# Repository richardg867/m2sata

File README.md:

# M.2 SATA Port Reclaimer

This M.2 2280 M-key card allows you to reclaim SATA ports that your motherboard may have as part of the chipset, but are not broken out to SATA connectors since the chipset shares their pins with the M.2 slot's PCI Express lanes.

Each SATA port is connected to a data lane of the M.2 card, although not all motherboards and M.2 slots support more than one SATA port (lane 0); if you just want one port, this adapter can work, but there are off-the-shelf ones that will also do the job. Read on for compatibility information.

## Ordering

I am not going to be offering assembled boards for the foreseeable future, since shipping from Brazil is too expensive and takes too much paperwork. You can order boards from your PCB vendor of choice (Gerber files are in the `gerbers` directory) and assemble them yourself (no SMD work is required); **make sure the PCB thickness is 0.8mm** and the total size is 22mm x 80mm, and go for ENIG finish if possible for best signal integrity (standard HASL finish is untested).

## Bill of materials

The only BOM item is a vertical through-hole SATA data connector, quantity 1 to 4 according to your needs. I've had success with [**LCSC part C2926857**](https://lcsc.com/product-detail/Card-Edge-Connectors_LOTES-ABA-SAT-010-K15_C2926857.html), though replacements can be [easily found](https://gist.github.com/CRImier/d78ff224db0d781627f211ff5cede573), or even desoldered from a donor board. When considering a replacement, make sure its **retention pins are centered** (aligned with the data pins); some parts have one of the retention pins slightly offset.

## Motherboard support

This adapter is expected to work (i.e. provide access to more than one SATA port) on a **SATA+NVMe M.2 slot** on the motherboard platforms listed below. Note that actual compatibility is **at your own risk**; boards might use an external switch chip to route only a single SATA port to the M.2 slot, or they might not have the SATA/PCIe mode switching signals hooked up for all lanes, or the BIOS might not enable normally-unused SATA ports.

In my limited real world testing with the ASUS H170-PLUS D3 (2 SATA ports routed to a single M.2), a drive attached to the second port was not visible in BIOS menus, but it was still initialized by the BIOS and detected by the operating system.

* **Chipsets:**
  * **AMD B550:** Up to 2 ports (0 and 1) from a slot connected to the chipset ("Group 2" - second set of PCIe lanes).
  * **AMD X570, 600 series:** Up to 4 ports from a slot connected to the chipset (combo lanes: [X570](https://www.gamersnexus.net/images/media/2020/amd-chipsets-b550/amd-x570-pcie-lanes.png), [B650](https://images.anandtech.com/doci/17585/SoC_26.png), [X670](https://images.anandtech.com/doci/17585/SoC_25.png)\).
  * **Intel 300/400 series:** Up to 4 ports from a slot connected to the chipset ([HSIO lanes 14-17, 28-21 or 22-25](https://www.intel.com/content/dam/www/public/us/en/documents/datasheets/300-series-chipset-pch-datasheet-vol-1.pdf#page=30)\).
  * **Intel 500/600/700 series:** Up to 4 ports from a slot connected to the chipset ([HSIO lanes 22-25, 26-29](https://edc.intel.com/content/www/us/en/design/ipla/software-development-platforms/client/platforms/alder-lake-desktop/intel-600-series-chipset-family-platform-controller-hub-pch-datasheet-volume/004/intel-600-series-chipset-family-pch/) or (500 only) [30-33](https://cdrdv2.intel.com/v1/dl/getContent/635218)\).
  * **Older stuff:** Some older motherboards which hijack multiple chipset SATA ports for M.2 can make use of this adapter. One example is the aforementioned ASUS H170-PLUS D3, which only exposes 4 of the 6 SATA ports provided by the H170 chipset, with the remaining 2 routed to M.2 slot lanes 0 and 1.
* **CPUs:**
  * **AMD AM4:** Up to 2 ports (0 and 1) from a slot connected to the CPU. Note that most motherboards already expose these (2 SATA ports shared with the CPU M.2 slot), making this adapter redundant.
  
### Very technical stuff: polarity inversion
  
One quirk of SATA is that its B (receive) differential pair has a different polarity than that of the A (transmit) pair or PCI Express RX/TX pairs, and unlike most PCIe implementations, it does *not* tolerate polarity inversion. Since the chipset's SerDes expects the same lane polarities in both SATA and PCIe modes, motherboards account for this quirk by inverting the polarity of the first SATA/PCIe lane going to the M.2 slot, to satisfy both SATA (cannot be inverted) and PCIe (can be inverted):

| M.2 pin | PCB | Chipset pin |
| ---: | :---: | :--- |
| PCIe TX0+ or SATA A+ | 🡸 | PCIe TX0+ or SATA A+ |
| PCIe TX0- or SATA A- | 🡸 | PCIe TX0- or SATA A- |
| PCIe **RX0+** or SATA **B-** | 🡾 | PCIe **RX0+** or SATA **B+** |
| PCIe **RX0-** or SATA **B+** | 🡽 | PCIe **RX0-** or SATA **B-** |
| PCIe TXn+ | 🡸 | PCIe TXn+ or SATA A+ |
| PCIe TXn- | 🡸 | PCIe TXn- or SATA A- |
| PCIe **RXn+** | 🡺 |PCIe RXn+ or SATA **B+** |
| PCIe **RXn-** | 🡺 | PCIe RXn- or SATA **B-** |

Since I have yet to see a motherboard which inverts the RX polarity on *all lanes* (not just lane 0), this card inverts it on lanes 1-3 so that they can work properly in SATA mode. If you get connection errors (Linux dmesg: `SATA link down (SStatus 1 SControl 300)`) on ports 1-3 even with high quality cables, you somehow have a motherboard which also inverts lanes 1-3; if you're feeling adventurous, the [jumperable](https://github.com/richardg867/m2sata/tree/jumperable) branch has a special variant of this card with jumper links to configure RX polarities at will.

## Acknowledgements

Huge thanks to [Arya](https://github.com/CRImier) for helping me with the design (using their [nvme_to_dual_ssd](https://github.com/CRImier/MyKiCad/tree/master/Laptop%20mods/nvme_to_dual_ssd) card as a base) and prototyping of this project.

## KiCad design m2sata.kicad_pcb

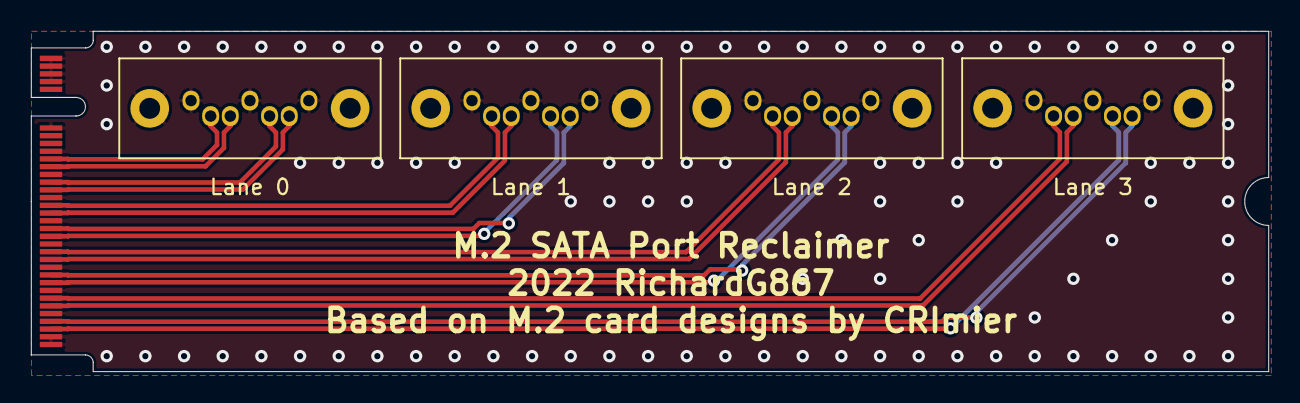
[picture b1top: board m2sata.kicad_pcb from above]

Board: 2 copper layers, 80.0 x 22.0 mm, 5 parts (0 on the bottom side), 17 nets.

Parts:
J1, J2, J3, J4: SATA; SATA-7_THT_VERT_1
U1: IN; NGFF_M

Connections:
/SATA1_A+: J1.2, U1.49 (PET0+/A+)
/SATA1_A-: J1.3, U1.47 (PET0-/A-)
/SATA1_B+: J1.6, U1.41 (PER0-/B+)
/SATA1_B-: J1.5, U1.43 (PER0+/B-)
/SATA2_A+: J2.2, U1.37 (PET1+)
/SATA2_A-: J2.3, U1.35 (PET1-)
/SATA2_B+: J2.6, U1.31 (PER1+)
/SATA2_B-: J2.5, U1.29 (PER1-)
/SATA3_A+: J3.2, U1.25 (PET2+)
/SATA3_A-: J3.3, U1.23 (PET2-)
/SATA3_B+: J3.6, U1.19 (PER2+)
/SATA3_B-: J3.5, U1.17 (PER2-)
/SATA4_A+: J4.2, U1.13 (PET3+)
/SATA4_A-: J4.3, U1.11 (PET3-)
/SATA4_B+: J4.6, U1.7 (PER3+)
/SATA4_B-: J4.5, U1.5 (PER3-)
GND: J1.1, J1.4, J1.7, J1.8, J1.9, J2.1, J2.4, J2.7, J2.8, J2.9, J3.1, J3.4, J3.7, J3.8, J3.9, J4.1, J4.4, J4.7, J4.8, J4.9, U1.1 (C3), U1.3 (GND), U1.9 (GND), U1.15 (GND), U1.21 (C0), U1.27 (GND), U1.33 (GND), U1.39 (GND), U1.45 (GND), U1.51 (GND), U1.57 (GND), U1.69 (C1), U1.71 (GND), U1.73 (GND), U1.75 (C2)

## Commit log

2022-10-29 Add initial readme
2022-10-29 Add placeholder image
2022-10-29 Finish readme for now
2022-10-29 Clarify gerbers presence and some other stuff
2022-10-29 Add files
2022-10-29 Add GPLv3 that I forgot about
2022-11-08 Add brokenness notice
2022-11-08 Elaborate on polarity issues
2022-11-10 Add jumperable version
2022-11-10 Apply polarity swap to secondary lanes
2022-11-10 Add new KiCad stuff to gitignore
2022-11-11 Update readme for polarity swap
2022-11-11 Bad cables also exist...
2022-11-11 Add jumperable version readme
2022-11-11 Remove reference designators that were still present
2022-11-11 Update gerbers for main branch
2022-11-11 Update gerbers for jumperable branch
2022-11-11 Add direct main readme link
2022-11-11 Readme compatibility tweaks
2022-11-11 Fix readme signal table mistake
2022-11-11 Fix ground plane breaks at the polarity vias
